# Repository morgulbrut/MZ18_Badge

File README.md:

# MZ18_Badge

## Idea

 * ESP32 or ATSAMD21
 * Micropython or CircuitPython (or Arduino or Forth or Lua or Javascript ;))
 * CMWX1ZZABZ-078 AKA Murata module for LoRa Connectivity, using STs AT-Slave
 * Oled display and some LEDs
 * Maybe one or two sensors (BMP/E 280 for example)
 
## Projectplan
 * Oct 17: Prototype 1 design finished, featuring ESP32 and ATSAMD21 footprints, to test both. 0603 parts to be able to handsolder.
 * Nov, Dec 17: Prototype 1 manufactured and tested and decision which sensors should be used
 * Jan 18: Design freeze Proto 2.
 * Feb, March 18: Proto 2 manufactured and tested.
 * April 18: Design freeze Final.
 * May 18: Final produced.

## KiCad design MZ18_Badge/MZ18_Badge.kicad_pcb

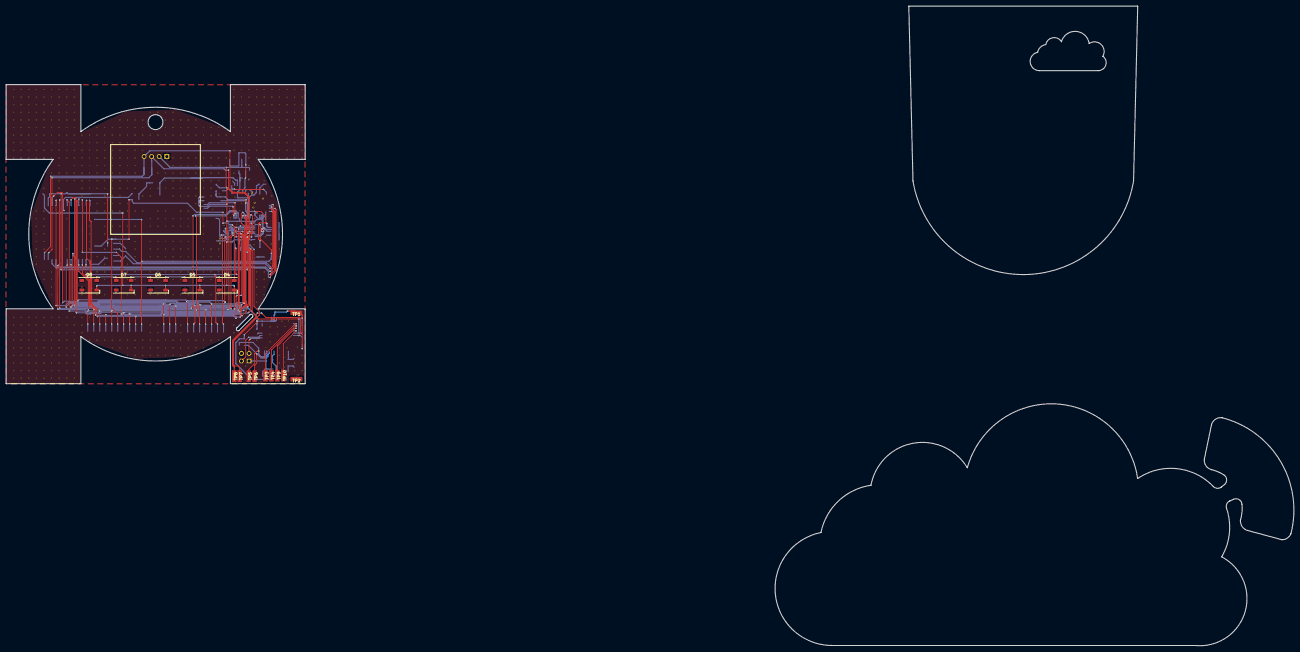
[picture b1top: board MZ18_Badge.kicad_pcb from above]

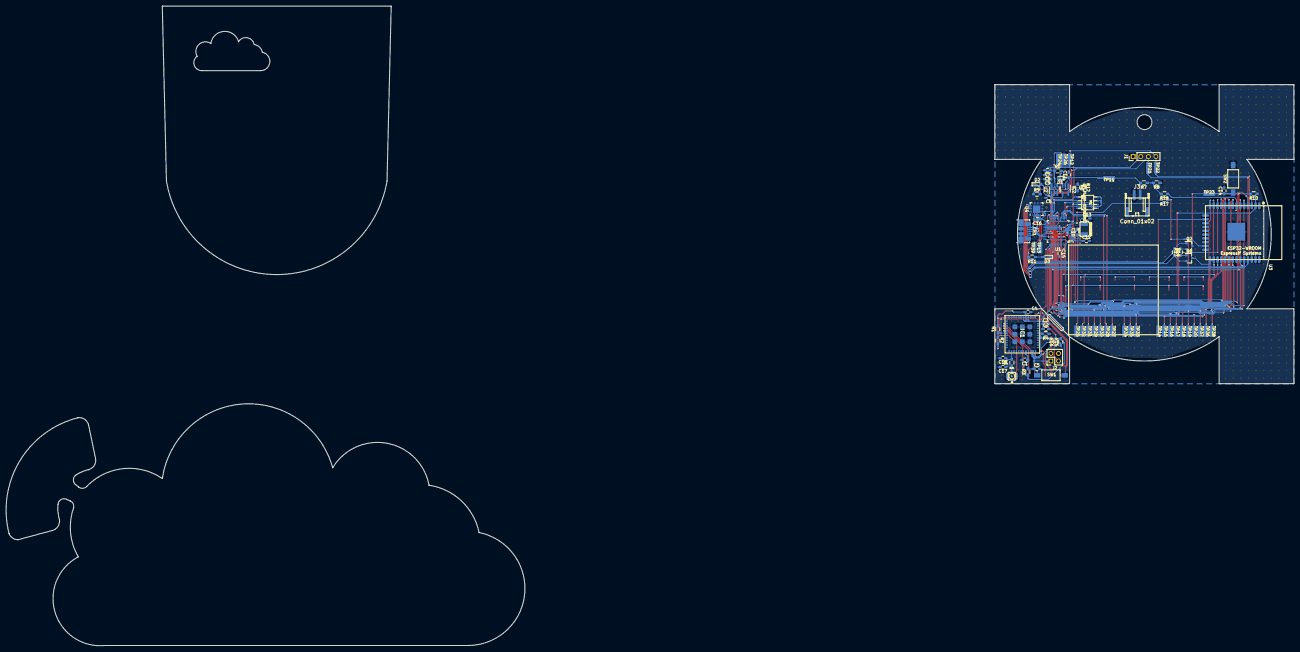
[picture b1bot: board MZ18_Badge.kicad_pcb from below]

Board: 2 copper layers, 100.0 x 100.0 mm, 811 parts (86 on the bottom side), 70 nets.

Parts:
C1, C3, C5, C8, C10, C14, C15, C17, C18: 1u; C_0603_HandSoldering
C2, C6, C7, C9, C11, C16: 10u; C_0603_HandSoldering
C4: 100n; C_0603_HandSoldering
C12, C13: 22p; C_0603_HandSoldering
CN1: USBMINIB; USB_Micro-B_Molex_47346-0001
D1: SCHOTTKY-DIODEAG; D_0603
D2, D3: LED; LED_0603_HandSoldering
D4, D5, D6, D7, D8: Neopixel_THT; LED_WS2812B-PLCC4
IC1: CMWX1ZZABZ-078
IC2: MCP73831_OT; SOT-23-5_HandSoldering
J1: Conn_01x04; Socket_Strip_Straight_1x04_Pitch2.54mm
J2: Conn_01x04; Socket_Strip_Straight_2x02_Pitch2.54mm
J3: Conn_01x02; s2b-ph-sm4-tb
J5: U.FL; coaxial_u.fl-r-smt-1
L1: INDUCTOR; L_0603_HandSoldering
M1: SPI_FLASH-X25XXSMD; so-8
Q1, Q2: MMBT2222; SOT-23
R1, R2, R5, R7, R8, R15, R16: 100k; R_0603_HandSoldering
R3, R4, R6, R10, R12, R13, R14: 10k; R_0603_HandSoldering
R9, R11: 1k1; R_0603_HandSoldering
R17, R18: 0; R_0603_HandSoldering
SW1, SW2: SW_Push; SW_SPST_FSMSM
TP1, TP2, TP3, TP4, TP5, TP6, TP7, TP8, TP9, TP10, TP11, TP12, TP13, TP14, TP15, TP16, TP17, TP18, TP19, TP20, TP21, TP22, TP23, TP24, TP25, TP26, TP27, TP28, TP29, TP30, TP31, TP32, TP33, TP34, TP35, TP36, TP37, TP38, TP39: §; Solderpad
U1: ATSAMD21G-A; TQFP-48_7x7mm_Pitch0.5mm
U2: SPX3819M5-L-3-3; SOT-23-5_HandSoldering
U3: ESP32-WROOM
U4: CP2104; QFN-24-1EP_4x4mm_Pitch0.5mm
V1_11, V1_12, V1_13, V1_14, V1_15, V1_16, V1_17, V1_18, V1_19, V1_20, V1_41, V1_42, V1_43, V1_44, V1_45, V1_46, V1_47, V1_48, V1_49, V2_11, V2_12, V2_13, V2_14, V2_15, V2_16, V2_17, V2_18, V2_19, V2_20, V2_41, V2_42, V2_43, V2_44, V2_45, V2_46, V2_47, V2_48, V2_49, V3_11, V3_12, V3_13, V3_14, V3_15, V3_16, V3_17, V3_18, V3_19, V3_20, V3_41, V3_42, V3_43, V3_44, V3_45, V3_46, V3_47, V3_48, V3_49, V4_11, V4_12, V4_13, V4_14, V4_15, V4_16, V4_17, V4_18, V4_19, V4_20, V4_27, V4_28, V4_29, V4_30, V4_31, V4_32, V4_33, V4_34, V4_41, V4_42, V4_43, V4_44, V4_45, V4_46, V4_47, V4_48, V4_49, V5_11, V5_12, V5_13, V5_14, V5_15, V5_16, V5_17, V5_18, V5_19, V5_20, V5_24, V5_27, V5_28, V5_29, V5_30, V5_31, V5_32, V5_35, V5_36, V5_41, V5_42, V5_43, V5_44, V5_45, V5_46, V5_47, V5_48, V5_49, V6_11, V6_12, V6_13, V6_14, V6_15, V6_16, V6_17, V6_18, V6_19, V6_20, V6_22, V6_35, V6_36, V6_37, V6_38, V6_41, V6_42, V6_43, V6_44, V6_45, V6_46, V6_47, V6_48, V6_49, V7_11, V7_12, V7_13, V7_14, V7_15, V7_16, V7_17, V7_18, V7_19, V7_20, V7_21, V7_22, V7_23, V7_24, V7_41, V7_42, V7_43, V7_44, V7_45, V7_46, V7_47, V7_48, V7_49, V8_11, V8_12, V8_13, V8_14, V8_15, V8_16, V8_17, V8_18, V8_19, V8_20, V8_22, V8_23, V8_28, V8_32, V8_41, V8_42, V8_43, V8_44, V8_45, V8_46, V8_47, V8_48, V8_49, V9_11, V9_12, V9_13, V9_14, V9_15, V9_16, V9_17, V9_18, V9_19, V9_20, V9_21, V9_22, V9_23, V9_41, V9_42, V9_43, V9_44, V9_45, V9_46, V9_47, V9_48, V9_49, V10_17, V10_18, V10_19, V10_20, V10_21, V10_22, V10_23, V10_24, V10_25, V10_37, V10_38, V10_41, V10_42, V10_43, V11_17, V11_18, V11_19, V11_20, V11_21, V11_22, V11_23, V11_24, V11_29, V11_30, V11_31, V11_32, V11_41, V11_44, V12_16, V12_17, V12_18, V12_19, V12_20, V12_21, V12_22, V12_23, V12_24, V12_26, V12_27, V12_33, V12_35, V12_38, V12_44, V13_16, V13_17, V13_18, V13_19, V13_20, V13_21, V13_22, V13_23, V13_24, V13_25, V13_26, V13_27, V13_29, V13_30, V13_32, V13_33, V13_34, V13_35, V13_36, V13_38, V13_44, V14_16, V14_17, V14_18, V14_19, V14_20, V14_21, V14_22, V14_23, V14_24, V14_25, V14_26, V14_27, V14_29, V14_30, V14_44, V14_45, V15_15, V15_16, V15_17, V15_18, V15_19, V15_20, V15_21, V15_22, V15_23, V15_24, V15_25, V15_26, V15_27, V15_29, V15_30, V15_31, V15_44, V15_45, V16_15, V16_16, V16_17, V16_18, V16_19, V16_20, V16_21, V16_22, V16_23, V16_24, V16_26, V16_27, V16_29, V16_30, V16_34, V16_35, V16_36, V16_38, V16_44, V16_45, V16_46, V17_15, V17_16, V17_17, V17_18, V17_19, V17_20, V17_21, V17_22, V17_23, V17_24, V17_27, V17_29, V17_30, V17_31, V17_32, V17_33, V17_35, V17_36, V17_38, V17_44, V17_45, V17_46, V18_15, V18_16, V18_17, V18_18, V18_19, V18_25, V18_27, V18_44, V18_45, V18_46, V19_14, V19_17, V19_18, V19_24, V19_25, V19_28, V19_29, V19_30, V19_31, V19_32, V19_33, V19_35, V19_38, V19_42, V19_43, V19_44, V19_45, V19_46, V20_14, V20_17, V20_18, V20_22, V20_24, V20_27, V20_28, V20_29, V20_30, V20_31, V20_32, V20_33, V20_35, V20_36, V20_38, V20_42, V20_43, V20_44, V20_45, V20_46, V21_14, V21_15, V21_16, V21_17, V21_18, V21_22, V21_23, V21_24, V21_27, V21_28, V21_29, V21_30, V21_31, V21_32, V21_33, V21_35, V21_38, V21_44, V21_45, V21_46, V22_14, V22_15, V22_16, V22_17, V22_18, V22_20, V22_21, V22_22, V22_23, V22_24, V22_25, V22_28, V22_29, V22_30, V22_31, V22_32, V22_33, V22_35, V22_36, V22_38, V22_44, V22_45, V22_46, V23_15, V23_16, V23_17, V23_18, V23_20, V23_21, V23_22, V23_23, V23_24, V23_25, V23_27, V23_28, V23_29, V23_30, V23_31, V23_32, V23_33, V23_35, V23_36, V23_38, V23_42, V23_43, V23_44, V23_45, V23_46, V24_15, V24_16, V24_17, V24_18, V24_20, V24_21, V24_22, V24_24, V24_25, V24_27, V24_28, V24_29, V24_30, V24_31, V24_32, V24_33, V24_35, V24_38, V24_44, V24_45, V24_46, V25_15, V25_16, V25_17, V25_18, V25_20, V25_21, V25_22, V25_24, V25_25, V25_26, V25_44, V25_45, V26_16, V26_17, V26_18, V26_20, V26_21, V26_22, V26_23, V26_24, V26_29, V26_29#2, V26_29#3, V26_29#4, V26_29#5, V26_29#6, V26_29#7, V26_29#8, V26_29#9, V26_29#10, V26_29#11, V26_29#12, V26_29#13, V26_30, V26_31, V26_32, V26_33, V26_35, V26_36, V26_38, V26_44, V26_45, V27_16, V27_17, V27_18, V27_20, V27_21, V27_22, V27_23, V27_24, V27_25, V27_25#2, V27_25#3, V27_32, V27_33, V27_35, V27_36, V27_38, V27_44, V28_16, V28_17, V28_18, V28_20, V28_21, V28_22, V28_23, V28_32, V28_33, V28_35, V28_38, V28_39, V28_44, V29_17, V29_18, V29_20, V29_38, V30_11, V30_12, V30_13, V30_14, V30_15, V30_16, V30_17, V30_18, V30_19, V30_22, V30_23, V30_42, V30_43, V31_11, V31_12, V31_13, V31_14, V31_15, V31_16, V31_17, V31_18, V31_19, V31_26, V32_11, V32_12, V32_13, V32_14, V32_15, V32_16, V32_17, V32_18, V32_19, V32_20, V32_21, V33_11, V33_12, V33_13, V33_14, V33_15, V33_16, V33_17, V33_18, V33_19, V33_20, V33_21, V33_35, V33_36, V33_37, V33_38, V33_39, V33_44, V34_11, V34_12, V34_13, V34_14, V34_15, V34_16, V34_17, V34_18, V34_19, V34_20, V34_23, V34_35, V34_36, V34_37, V34_38, V35_11, V35_12, V35_13, V35_14, V35_15, V35_16, V35_17, V35_18, V35_19, V35_20, V35_25, V36_11, V36_12, V36_13, V36_14, V36_15, V36_16, V36_17, V36_18, V36_19, V36_20, V36_32, V36_33, V36_33#2, V36_45, V36_46, V36_47, V36_47#2, V36_47#3, V36_47#4, V37_11, V37_12, V37_13, V37_14, V37_15, V37_16, V37_17, V37_18, V37_19, V37_20, V37_45, V37_47, V37_47#2, V37_47#3, V37_47#4, V37_47#5, V37_47#6, V37_47#7, V37_47#8, V38_11, V38_12, V38_13, V38_14, V38_15, V38_16, V38_17, V38_18, V38_19, V38_20, V38_46, V38_47, V38_48, V39_11, V39_12, V39_13, V39_14, V39_15, V39_16, V39_17, V39_18, V39_19, V39_20, V39_46, V39_46#2, V39_46#3, V39_46#4, V39_46#5, V39_46#6, V39_46#7, V39_46#8, V39_46#9, V39_46#10, V39_46#11, V39_46#12, V39_47, V39_48: AUTO_VIA; VIA_MATRIX
X1: XTALNX5032; crystal_smd_5x3.2mm

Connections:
3V: C1.1, C2.1, C3.1, C4.1, C7.1, C8.1, C9.1, C16.1, D4.3, D5.3, D6.3, D7.3, D8.3, IC1.4, IC1.5, IC1.6, IC1.32, IC1.48, J1.2, M1.3, M1.7, M1.8, R1.2, R2.2, R3.1, R10.1, R12.1, R15.2, R16.2, TP1.1, TP24.1, U1.6, U1.17, U1.36, U1.44, U2.5, U3.2, U4.5, U4.6, U4.7
/MISO_LO: IC1.15, TP4.1
/MOSI_LO: IC1.14, TP3.1
/NSS_LO: IC1.17, TP10.1
/SCK_LO: IC1.16, TP9.1
/SCL_LO: IC1.35, R16.1, TP6.1
/SDA_LO: IC1.36, R15.1, TP5.1
A0: TP27.1, U1.3, U3.11
A1: TP28.1, U1.7, U3.10
A2: TP29.1, U1.8, U3.6
A3: TP30.1, U1.9, U3.5
A4: TP31.1, U1.10, U3.4
A5: TP32.1, U1.47, U3.26
A13_I35: R18.1, U3.7
AREF: C10.1, TP25.1, U1.4
D0: TP36.1, U1.16, U3.27
D1: TP37.1, U1.15, U3.28
D1_FLASHMISO: M1.2, U1.23
D3_FLASHSCK: M1.6, U1.14
D4_FLASHMOSI: M1.5, U1.13
D5: TP20.1, U1.24, U3.13
D6: TP19.1, U1.29, U3.8
D8_NEOPIX: D4.4, U1.11
D9: R17.1, TP18.1, U1.12, U3.23
D10: TP17.1, U1.27, U3.9
D11: TP16.1, U1.25, U3.12
D12: TP15.1, U1.28, U3.14
D13: R11.2, TP14.1, U1.26, U3.16
D+: CN1.2, U1.34, U4.3
D-: CN1.3, U1.33, U4.4
DTR: Q1.2, R14.2, U4.23
EN: R5.1, TP12.1, U2.3
FLASH_CS: M1.1, R12.2, U1.22
GND: C1.2, C2.2, C3.2, C4.2, C5.2, C6.2, C7.2, C8.2, C9.2, C10.2, C11.2, C12.2, C13.2, C14.2, C15.2, C16.2, C17.2, C18.2, CN1.5, CN1.6, D3.1, D4.2, D5.2, D6.2, D7.2, D8.2, IC1.3, IC1.7, IC1.25, IC1.27, IC1.44, IC1.49, IC1.50, IC1.51, IC1.52, IC1.53, IC1.54, IC1.55, IC1.56, IC1.57, IC2.2, J1.1, J2.4, J3.1, J5.2, M1.4, R4.1, R6.1, R8.1, SW1.2, SW2.2, TP2.1, TP26.1, TP39.1, U1.5, U1.18, U1.35, U1.42, U2.2, U3.1, U3.15, U3.38, U3.39, U4.2, U4.25, V1_11.1, V1_12.1, V1_13.1, V1_14.1, V1_15.1, V1_16.1, V1_17.1, V1_18.1, V1_19.1, V1_20.1, V1_41.1, V1_42.1, V1_43.1, V1_44.1, V1_45.1, V1_46.1, V1_47.1, V1_48.1, V1_49.1, V2_11.1, V2_12.1, V2_13.1, V2_14.1, V2_15.1, V2_16.1, V2_17.1, V2_18.1, V2_19.1, V2_20.1, V2_41.1, V2_42.1, V2_43.1, V2_44.1, V2_45.1, V2_46.1, V2_47.1, V2_48.1, V2_49.1, V3_11.1, V3_12.1, V3_13.1, V3_14.1, V3_15.1, V3_16.1, V3_17.1, V3_18.1, V3_19.1, V3_20.1, V3_41.1, V3_42.1, V3_43.1, V3_44.1, V3_45.1, V3_46.1, V3_47.1, V3_48.1, V3_49.1, V4_11.1, V4_12.1, V4_13.1, V4_14.1, V4_15.1, V4_16.1, V4_17.1, V4_18.1, V4_19.1, V4_20.1, V4_27.1, V4_28.1, V4_29.1, V4_30.1, V4_31.1, V4_32.1, V4_33.1, V4_34.1, V4_41.1, V4_42.1, V4_43.1, V4_44.1, V4_45.1, V4_46.1, V4_47.1, V4_48.1, V4_49.1, V5_11.1, V5_12.1, V5_13.1, V5_14.1, V5_15.1, V5_16.1, V5_17.1, V5_18.1, V5_19.1, V5_20.1, V5_24.1, V5_27.1, V5_28.1, V5_29.1, V5_30.1, V5_31.1, V5_32.1, V5_35.1, V5_36.1, V5_41.1, V5_42.1, V5_43.1, V5_44.1, V5_45.1, V5_46.1, V5_47.1, V5_48.1, V5_49.1, V6_11.1, V6_12.1, V6_13.1, V6_14.1, V6_15.1, V6_16.1, V6_17.1, V6_18.1, V6_19.1, V6_20.1, V6_22.1, V6_35.1, V6_36.1, V6_37.1, V6_38.1, V6_41.1, V6_42.1, V6_43.1, V6_44.1, V6_45.1, V6_46.1, V6_47.1, V6_48.1, V6_49.1, V7_11.1, V7_12.1, V7_13.1, V7_14.1, V7_15.1, V7_16.1, V7_17.1, V7_18.1, V7_19.1, V7_20.1, V7_21.1, V7_22.1, V7_23.1, V7_24.1, V7_41.1, V7_42.1, V7_43.1, V7_44.1, V7_45.1, V7_46.1, V7_47.1, V7_48.1, V7_49.1, V8_11.1, V8_12.1, V8_13.1, V8_14.1, V8_15.1, V8_16.1, V8_17.1, V8_18.1, V8_19.1, V8_20.1, V8_22.1, V8_23.1, V8_28.1, V8_32.1, V8_41.1, V8_42.1, V8_43.1, V8_44.1, V8_45.1, V8_46.1, V8_47.1, V8_48.1, V8_49.1, V9_11.1, V9_12.1, V9_13.1, V9_14.1, V9_15.1, V9_16.1, V9_17.1, V9_18.1, V9_19.1, V9_20.1, V9_21.1, V9_22.1, V9_23.1, V9_41.1, V9_42.1, V9_43.1, V9_44.1, V9_45.1, V9_46.1, V9_47.1, V9_48.1, V9_49.1, V10_17.1, V10_18.1, V10_19.1, V10_20.1, V10_21.1, V10_22.1, V10_23.1, V10_24.1, V10_25.1, V10_37.1, V10_38.1, V10_41.1, V10_42.1, V10_43.1, V11_17.1, V11_18.1, V11_19.1, V11_20.1, V11_21.1, V11_22.1, V11_23.1, V11_24.1, V11_29.1, V11_30.1, V11_31.1, V11_32.1, V11_41.1, V11_44.1, V12_16.1, V12_17.1, V12_18.1, V12_19.1, V12_20.1, V12_21.1, V12_22.1, V12_23.1, V12_24.1, V12_26.1, V12_27.1, V12_33.1, V12_35.1, V12_38.1, V12_44.1, V13_16.1, V13_17.1, V13_18.1, V13_19.1, V13_20.1, V13_21.1, V13_22.1, V13_23.1, V13_24.1, V13_25.1, V13_26.1, V13_27.1, V13_29.1, V13_30.1, V13_32.1, V13_33.1, V13_34.1, V13_35.1, V13_36.1, V13_38.1, V13_44.1, V14_16.1, V14_17.1, V14_18.1, V14_19.1, V14_20.1, V14_21.1, V14_22.1, V14_23.1, V14_24.1, V14_25.1, V14_26.1, V14_27.1, V14_29.1, V14_30.1, V14_44.1, V14_45.1, V15_15.1, V15_16.1, V15_17.1, V15_18.1, V15_19.1, V15_20.1, V15_21.1, V15_22.1, V15_23.1, V15_24.1, V15_25.1, V15_26.1, V15_27.1, V15_29.1, V15_30.1, V15_31.1, V15_44.1, V15_45.1, V16_15.1, V16_16.1, V16_17.1, V16_18.1, V16_19.1, V16_20.1, V16_21.1, V16_22.1, V16_23.1, V16_24.1, V16_26.1, V16_27.1, V16_29.1, V16_30.1, V16_34.1, V16_35.1, V16_36.1, V16_38.1, V16_44.1, V16_45.1, V16_46.1, V17_15.1, V17_16.1, V17_17.1, V17_18.1, V17_19.1, V17_20.1, V17_21.1, V17_22.1, V17_23.1, V17_24.1, V17_27.1, V17_29.1, V17_30.1, V17_31.1, V17_32.1, V17_33.1, V17_35.1, V17_36.1, V17_38.1, V17_44.1, V17_45.1, V17_46.1, V18_15.1, V18_16.1, V18_17.1, V18_18.1, V18_19.1, V18_25.1, V18_27.1, V18_44.1, V18_45.1, V18_46.1, V19_14.1, V19_17.1, V19_18.1, V19_24.1, V19_25.1, V19_28.1, V19_29.1, V19_30.1, V19_31.1, V19_32.1, V19_33.1, V19_35.1, V19_38.1, V19_42.1, V19_43.1, V19_44.1, V19_45.1, V19_46.1, V20_14.1, V20_17.1, V20_18.1, V20_22.1, V20_24.1, V20_27.1, V20_28.1, V20_29.1, V20_30.1, V20_31.1, V20_32.1, V20_33.1, V20_35.1, V20_36.1, V20_38.1, V20_42.1, V20_43.1, V20_44.1, V20_45.1, V20_46.1, V21_14.1, V21_15.1, V21_16.1, V21_17.1, V21_18.1, V21_22.1, V21_23.1, V21_24.1, V21_27.1, V21_28.1, V21_29.1, V21_30.1, V21_31.1, V21_32.1, V21_33.1, V21_35.1, V21_38.1, V21_44.1, V21_45.1, V21_46.1, V22_14.1, V22_15.1, V22_16.1, V22_17.1, V22_18.1, V22_20.1, V22_21.1, V22_22.1, V22_23.1, V22_24.1, V22_25.1, V22_28.1, V22_29.1, V22_30.1, V22_31.1, V22_32.1, V22_33.1, V22_35.1, V22_36.1, V22_38.1, V22_44.1, V22_45.1, V22_46.1, V23_15.1, V23_16.1, V23_17.1, V23_18.1, V23_20.1, V23_21.1, V23_22.1, V23_23.1, V23_24.1, V23_25.1, V23_27.1, V23_28.1, V23_29.1, V23_30.1, V23_31.1, V23_32.1, V23_33.1, V23_35.1, V23_36.1, V23_38.1, V23_42.1, V23_43.1, V23_44.1, V23_45.1, V23_46.1, V24_15.1, V24_16.1, V24_17.1, V24_18.1, V24_20.1, V24_21.1, V24_22.1, V24_24.1, V24_25.1, V24_27.1, V24_28.1, V24_29.1, V24_30.1, V24_31.1, V24_32.1, V24_33.1, V24_35.1, V24_38.1, V24_44.1, V24_45.1, V24_46.1, V25_15.1, V25_16.1, V25_17.1, V25_18.1, V25_20.1, V25_21.1, V25_22.1, V25_24.1, V25_25.1, V25_26.1, V25_44.1, V25_45.1, V26_16.1, V26_17.1, V26_18.1, V26_20.1, V26_21.1, V26_22.1, V26_23.1, V26_24.1, V26_29.1, V26_29#2.1, V26_29#3.1, V26_29#4.1, V26_29#5.1, V26_29#6.1, V26_29#7.1, V26_29#8.1, V26_29#9.1, V26_29#10.1, V26_29#11.1, V26_29#12.1, V26_29#13.1, V26_30.1, V26_31.1, V26_32.1, V26_33.1, V26_35.1, V26_36.1, V26_38.1, V26_44.1, V26_45.1, V27_16.1, V27_17.1, V27_18.1, V27_20.1, V27_21.1, V27_22.1, V27_23.1, V27_24.1, V27_25.1, V27_25#2.1, V27_25#3.1, V27_32.1, V27_33.1, V27_35.1, V27_36.1, V27_38.1, V27_44.1, V28_16.1, V28_17.1, V28_18.1, V28_20.1, V28_21.1, V28_22.1, V28_23.1, V28_32.1, V28_33.1, V28_35.1, V28_38.1, V28_39.1, V28_44.1, V29_17.1, V29_18.1, V29_20.1, V29_38.1, V30_11.1, V30_12.1, V30_13.1, V30_14.1, V30_15.1, V30_16.1, V30_17.1, V30_18.1, V30_19.1, V30_22.1, V30_23.1, V30_42.1, V30_43.1, V31_11.1, V31_12.1, V31_13.1, V31_14.1, V31_15.1, V31_16.1, V31_17.1, V31_18.1, V31_19.1, V31_26.1, V32_11.1, V32_12.1, V32_13.1, V32_14.1, V32_15.1, V32_16.1, V32_17.1, V32_18.1, V32_19.1, V32_20.1, V32_21.1, V33_11.1, V33_12.1, V33_13.1, V33_14.1, V33_15.1, V33_16.1, V33_17.1, V33_18.1, V33_19.1, V33_20.1, V33_21.1, V33_35.1, V33_36.1, V33_37.1, V33_38.1, V33_39.1, V33_44.1, V34_11.1, V34_12.1, V34_13.1, V34_14.1, V34_15.1, V34_16.1, V34_17.1, V34_18.1, V34_19.1, V34_20.1, V34_23.1, V34_35.1, V34_36.1, V34_37.1, V34_38.1, V35_11.1, V35_12.1, V35_13.1, V35_14.1, V35_15.1, V35_16.1, V35_17.1, V35_18.1, V35_19.1, V35_20.1, V35_25.1, V36_11.1, V36_12.1, V36_13.1, V36_14.1, V36_15.1, V36_16.1, V36_17.1, V36_18.1, V36_19.1, V36_20.1, V36_32.1, V36_33.1, V36_33#2.1, V36_45.1, V36_46.1, V36_47.1, V36_47#2.1, V36_47#3.1, V36_47#4.1, V37_11.1, V37_12.1, V37_13.1, V37_14.1, V37_15.1, V37_16.1, V37_17.1, V37_18.1, V37_19.1, V37_20.1, V37_45.1, V37_47.1, V37_47#2.1, V37_47#3.1, V37_47#4.1, V37_47#5.1, V37_47#6.1, V37_47#7.1, V37_47#8.1, V38_11.1, V38_12.1, V38_13.1, V38_14.1, V38_15.1, V38_16.1, V38_17.1, V38_18.1, V38_19.1, V38_20.1, V38_46.1, V38_47.1, V38_48.1, V39_11.1, V39_12.1, V39_13.1, V39_14.1, V39_15.1, V39_16.1, V39_17.1, V39_18.1, V39_19.1, V39_20.1, V39_46.1, V39_46#2.1, V39_46#3.1, V39_46#4.1, V39_46#5.1, V39_46#6.1, V39_46#7.1, V39_46#8.1, V39_46#9.1, V39_46#10.1, V39_46#11.1, V39_46#12.1, V39_47.1, V39_48.1
GPIO0: Q1.3, U3.25
IO21: TP38.1, U3.33
MISO: TP35.1, U1.21, U3.31
MOSI: TP34.1, U1.19, U3.30
NRESET: C14.1, Q2.3, R10.2, SW2.1, TP23.1, U1.40, U3.3
NRST_LO: C5.1, IC1.34, J2.1, R3.2, SW1.1
unnamed: C12.1, U1.1
unnamed: C13.1, U1.2
unnamed: C15.1, U1.43
unnamed: C17.1, J5.1, L1.1
unnamed: C18.1, IC1.26, L1.2
unnamed: D2.1, R9.2
unnamed: D3.2, R11.1
unnamed: D4.1, D5.4
unnamed: D5.1, D6.4
unnamed: D6.1, D7.4
unnamed: D7.1, D8.4
unnamed: IC1.43, R4.2
unnamed: IC1.46, IC1.47
unnamed: IC2.1, R9.1
unnamed: IC2.5, R6.2
unnamed: Q1.1, R13.1
unnamed: Q2.1, R14.1
unnamed: R7.1, R8.2, R17.2, R18.2
RTS: Q2.2, R13.2, U4.19
RXD: IC1.19, R2.1, TP8.1, U1.38
RXD0: U3.34, U4.20
SCK: TP33.1, U1.20, U3.29
SCL: J1.3, TP21.1, U1.32, U3.36
SDA: J1.4, TP22.1, U1.31, U3.37
SWDCLK_LO: IC1.42, J2.2
SWDIO_LO: IC1.41, J2.3
TXD: IC1.18, R1.1, TP7.1, U1.37
TXD0: U3.35, U4.21
VBAT: C11.1, IC2.3, J3.2, R7.2, TP11.1
VUSB: C6.1, CN1.1, D1.2, D2.2, IC2.4, R5.2, TP13.1, U2.1, U4.8

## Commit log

2017-10-06 Second board outline idea added
2017-10-06 Moved files
2017-10-06 Schematics done
2017-10-16 Desig (almost) done
    Via stiching not yet done
2017-10-16 Output done
2017-10-16 cmp.flile added
2017-10-16 Via stiching and LoRa part
2017-12-07 first submission to pcbway
2019-04-10 [ImgBot] Optimize images
    *Total -- 1,034.97kb -> 969.16kb (6.36%)
    /MZ18_Badge/BO_Badge.png -- 17.15kb -> 7.65kb (55.42%)
    /MZ18_Badge/Smaky_100_IMG_4149.jpg -- 1,017.83kb -> 961.51kb (5.53%)
